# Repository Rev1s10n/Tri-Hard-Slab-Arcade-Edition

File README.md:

# Tri-Hard Slab: Arcade Edition
## **English | [繁體中文](README_zh-TW.md)**
A follow up from my previous [build](https://github.com/Rev1s10n/Tri-Hard-slab-v2), powered by [GP2040-CE](https://gp2040-ce.info/) firmware (v.0.7.10) with custom 16 buttons layout.<br>
This time it's made with Cherry MX switches instead of Kailh Choc switches, and CNC aluminum case with acrylic top layer for art insert.

**I would suggest not build this yourself at this momemnt as there's some design flaws, which makes it really difficult to assemble**<br>
**A new case design might come in the future**

## Key features and specs
- Dimensions: 270x200x24.1mm (including custom laser cut foampad)
- Weights: 1.3 kg
- Single CNC alumium case with laser cut acrylic sheet top panel and CNC polycarbonate mounting plate.
- Main key switches: any Cherry MX style switches, with hot swap sockets and Punk Workshop's key caps (25.5mm)
- Double RGB LED per key, and 4 RGB LEDs for player number indication.
- 2 USB Type-A connectors for passthrough devices, with slide switches to choose which one to activate.
- 1.3 inches OLED display.
- 3 slide switches on the top side for focus, SOCD and DP / LS / RS switch.
- Additional up button for general gaming purpose, and function key for quick profile swap.

Close up photos and feature explain:

_Fully redesigned circuit board with custom layout for my own comfort, passthrough device is now within the enclosure_

_1 additional tactile switch for function key, and custom display layout_

_Passthrough device can be selected with this slide switch_

_This time these switches is on the top side_

## Production files
Simply download all production files via Hardware files folder, and utilize services like JLCPCB (which is what I did in this case) to order the board.<br>
The board need standard PCBA for certain components. JLCPCB might told you there's some error (2 pins on 1 pad) but it's intended, and they'll make the board nevertheless.<br>
As for the case and acrylics / PC sheet, there's a step file for CNC aluminum case, 2 dxf files for laser cut acrylic, 1 dxf for CNC PC mounting plate.

## Source files
The Tri-Hard Slab AE is made with Autodesk Fusion 360 and KiCad 7.0.<br>
Everything is under Source files, include a rough Fusion 360 sketch which is the base of all laser-cut dxf files, step file and for KiCad to align things up.

## Assemble and settings
This is a bit tricky compare to original build.<br>
Here's some additional things you need to complete this build:
- Cherry MX switches, or any MX compatible switches, I use Cherry MX Black in this case.
- 16 Kailh MX hot swap socket (PG1511).
- 1.3 inches OLED display, make sure the pin order and set the slide switch accordingly.
- 9 M6 sex bolt / Chicago screws, with additional sink head screws
- Tons of hard and soft PVC washer (M6 sizes, 1mm thick) and NBR o-ring (6*2mm) for spacing.
- Custom laser cut EVA foams

There's a custom firmware with custom button layout for OLED display, and here's the GPIO pin mapping for reference:
|Keys|GPIO|
|-|-|
|Up|11|
|Down|9|
|Left|8|
|Right|10|
|B1/1K/A/Circle|13|
|B2/2K/B/Cross|15|
|B3/1P/X/Square|14|
|B4/2P/Y/Triangle|20|
|L1/4P/LB|18|
|R1/3P/RB|19|
|L2/4K/LT|17|
|R2/3K/RT|16|
|S1/Select/Back|1|
|S2/Start|3|
|L3/LS|21|
|R3/RS|22|
|A1/Home/Guide|2|
|A2/Touch|12|
|Function|0|
|Dual Direction Up|7|

Additional GPIO pin mapping and LED index for other features:
|Features|GPIO and index|
|-|-|
|RGB LED Data Pin|6|
|Player LEDs|starting from 32 to 35|
|Display SDA|4|
|Display SCL|5|
|Joystick Selection Slider Pin 1|26|
|Joystick Selection Slider Pin 2|25|
|SOCD Cleaning Mode Selection Slider Pin 1|28|
|SOCD Cleaning Mode Selection Slider Pin 2|27|
|PS Passthrough D+|23|
|PS Passthrough D-|24|
|Focus Mode Pin|29|

After load the setting file, there's 4 different profiles and there's shortcut combination to switch to any profile:
|Profile|Key combination|
|-|-|
|Profile 1 (Default pin mapping)|FN + S1 + S2 + 1P|
|Profile 2 (Unbind DDI Up)|FN + S1 + S2 + 2P|
|Profile 3 (Bind A2 as S1 for PC/Xbox)|FN + S1 + S2 + 3P|
|Profile 4 (Profile 3 + Unbind DDI Up)|FN + S1 + S2 + 4P|

## Custom artwork

You can download the PSD file and dxf drawing reference in Custom artwork template folder for top panel.<br>
Print it out and insert the artwork between 02 and 03 acrylic layers.

## Attribution
You're free to use this design as long as you credit to this page.<br>
[Licensed under CC BY 4.0](https://creativecommons.org/licenses/by/4.0/)

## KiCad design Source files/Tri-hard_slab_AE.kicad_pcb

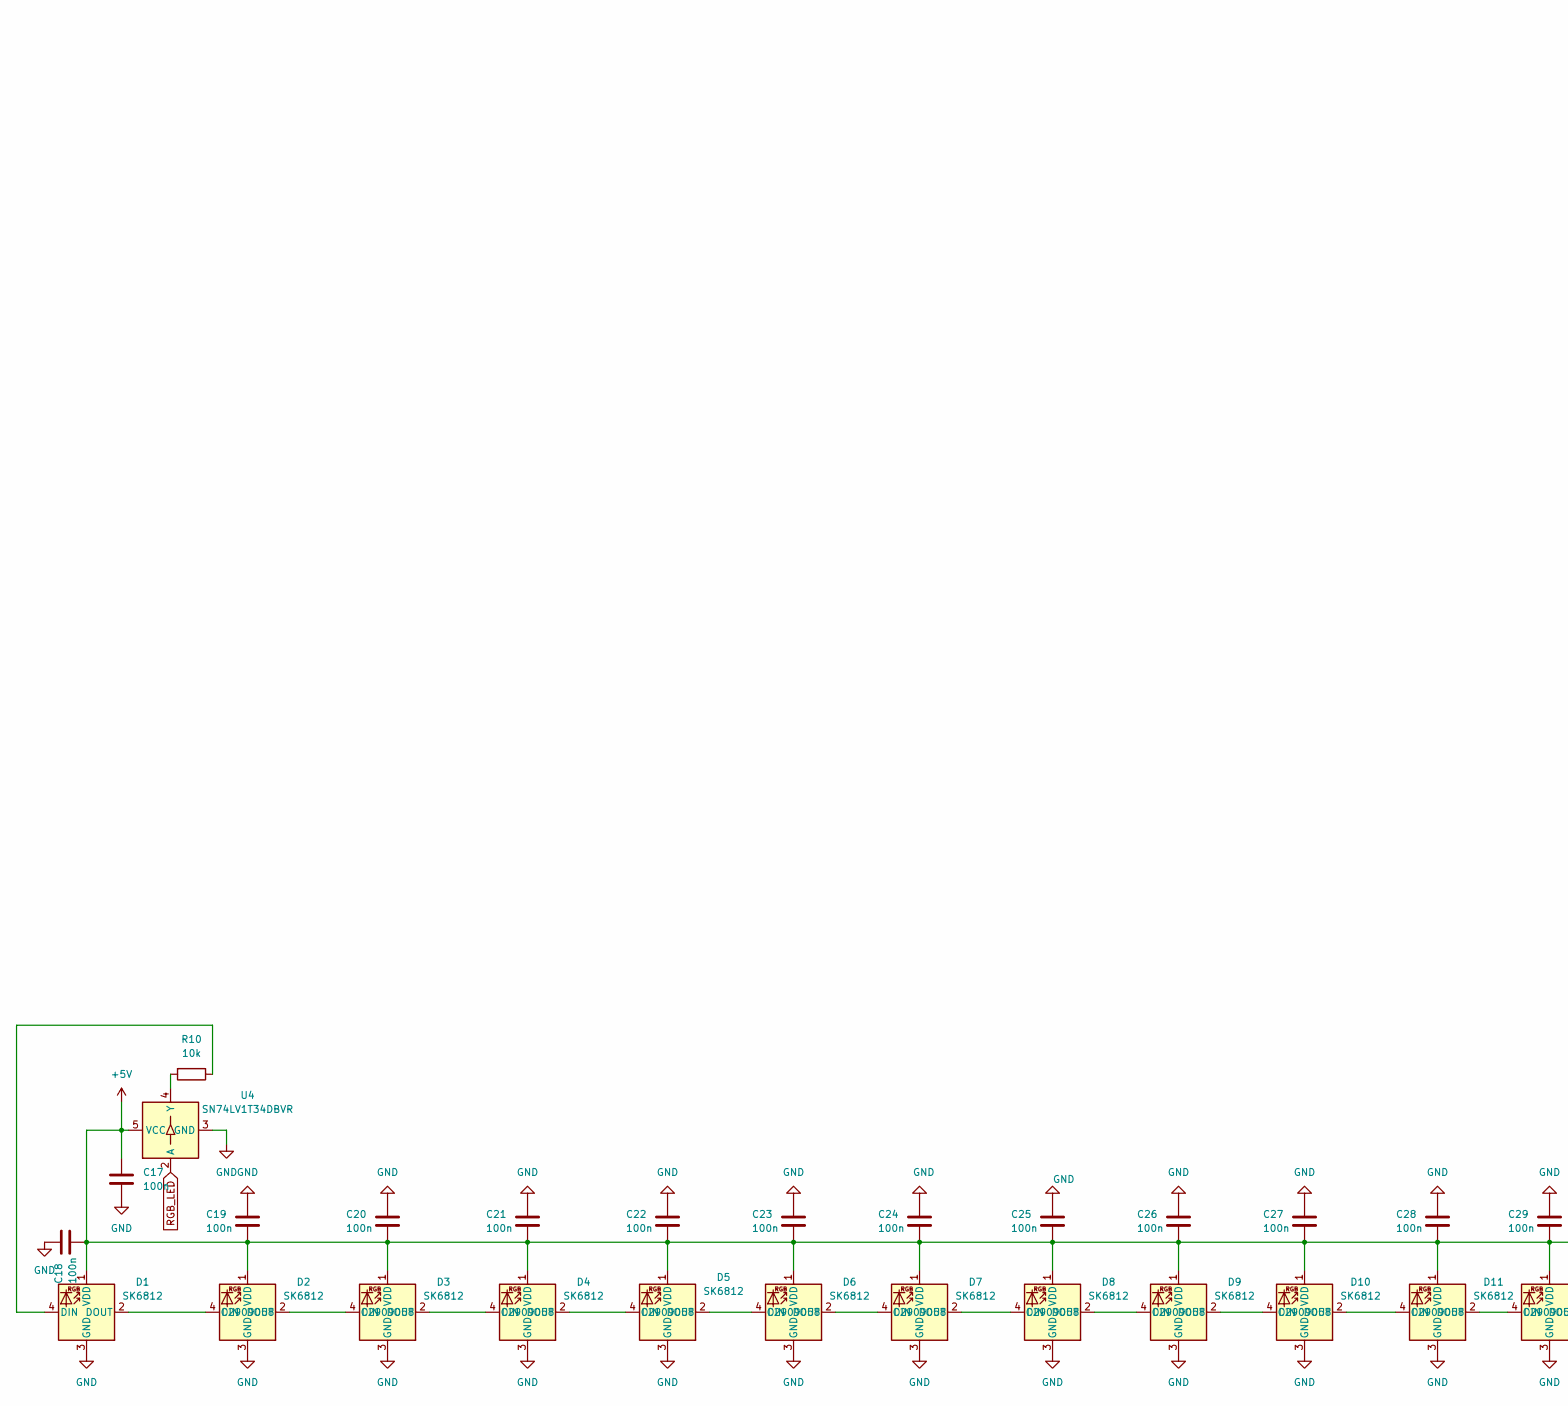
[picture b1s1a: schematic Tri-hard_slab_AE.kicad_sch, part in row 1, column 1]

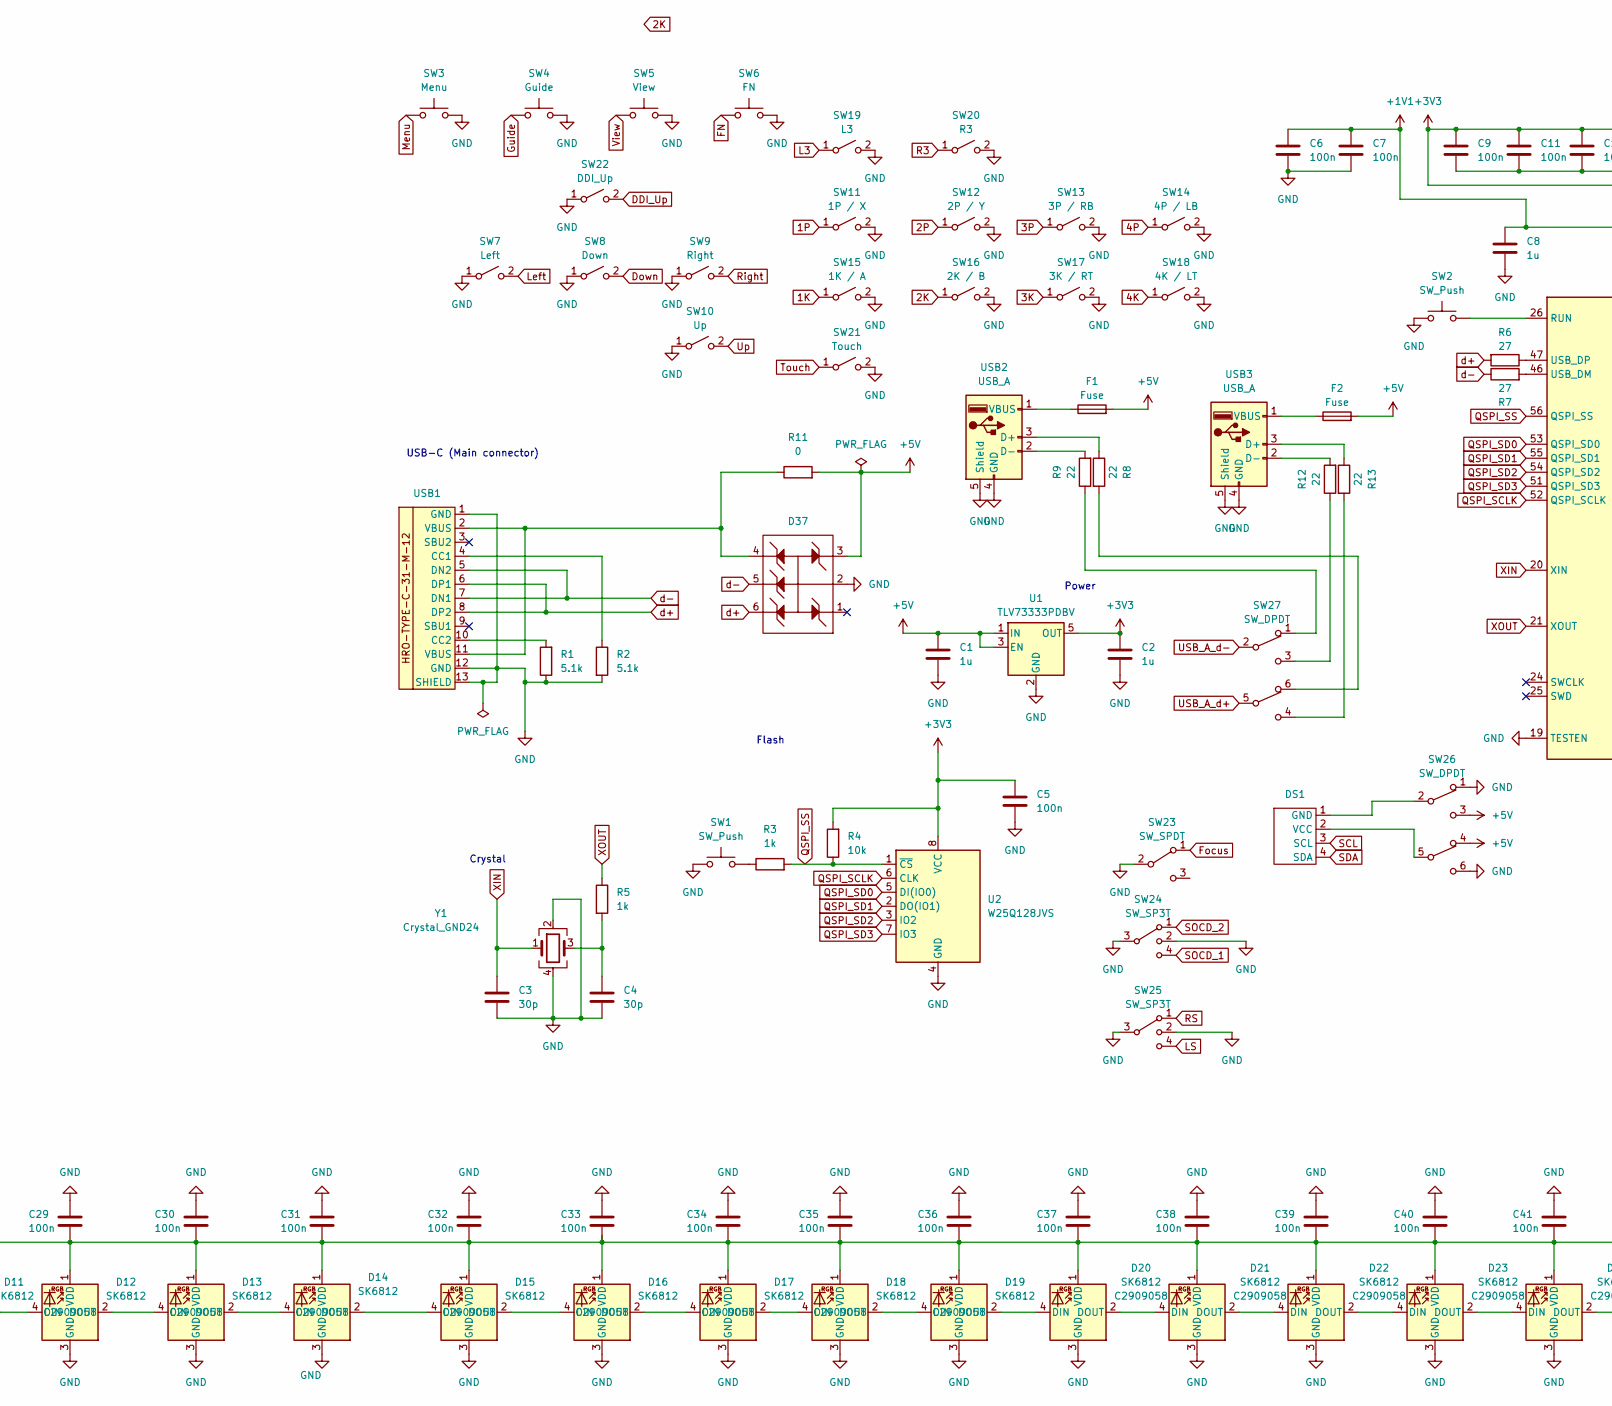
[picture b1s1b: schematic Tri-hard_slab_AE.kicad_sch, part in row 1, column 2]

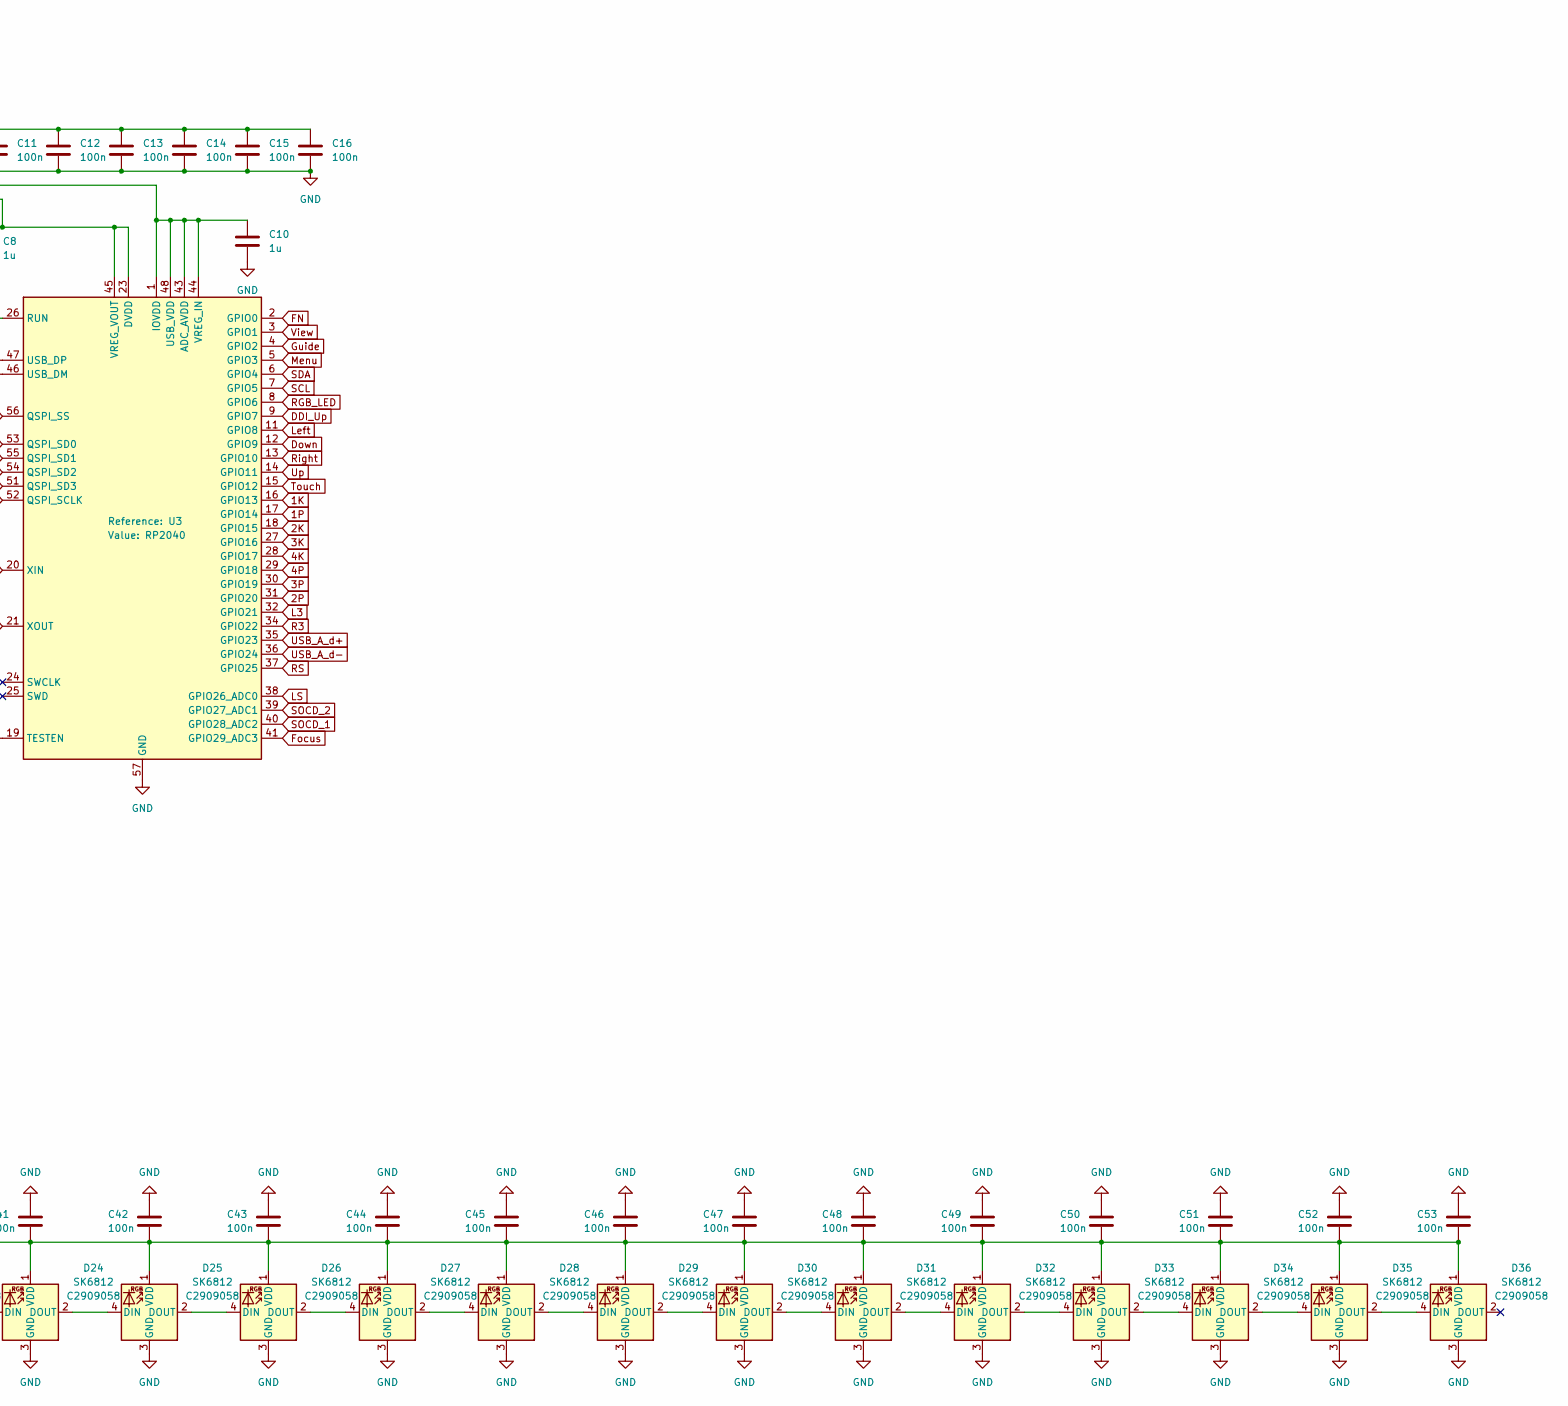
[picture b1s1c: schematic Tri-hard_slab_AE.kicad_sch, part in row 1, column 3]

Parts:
C1, C2, C8, C10: 1u; C_0402_1005Metric; LCSC C52923
C3, C4: 30p; C_0402_1005Metric; LCSC C161152
C5, C6, C7, C9, C11, C12, C13, C14, C15, C16, C17, C18, C19, C20, C21, C22, C23, C24, C25, C26, C27, C28, C29, C30, C31, C32, C33, C34, C35, C36, C37, C38, C39, C40, C41, C42, C43, C44, C45, C46, C47, C48, C49, C50, C51, C52, C53: 100n; C_0402_1005Metric; LCSC C1525
D1, D2, D3, D4, D5, D6, D7, D8, D9, D10, D11, D12, D13, D14, D15, D16, D17, D18, D19, D20, D21, D22, D23, D24, D25, D26, D27, D28, D29, D30, D31, D32, D33, D34, D35, D36: SK6812; SK6812-EC20; LCSC C2909058
D37: SOT-363_SC-70-6; LCSC C15879
DS1: 368030501246
F1, F2: Fuse; Fuse_0805_2012Metric; LCSC C116170
R1, R2: 5.1k; R_0402_1005Metric; LCSC C25905
R3, R5: 1k; R_0402_1005Metric; LCSC C11702
R4, R10: 10k; R_0402_1005Metric; LCSC C25744
R6, R7: 27; R_0402_1005Metric; LCSC C138021
R8, R9, R12, R13: 22; R_0603_1608Metric; LCSC C23345
R11: 0; R_0402_1005Metric; LCSC C17168
SW1, SW2: SW_Push; SKRAAKE010; LCSC C115354
SW3: Menu; TSF001A16026A; LCSC C2888706
SW4: Guide; TSF001A16026A; LCSC C2888706
SW5: View; TSF001A16026A; LCSC C2888706
SW6: FN; TSF001A16026A; LCSC C2888706
SW7: Left; SW_Hotswap_Kailh_MX_Plated
SW8: Down; SW_Hotswap_Kailh_MX_Plated
SW9: Right; SW_Hotswap_Kailh_MX_Plated
SW10: Up; SW_Hotswap_Kailh_MX_Plated
SW11: 1P / X; SW_Hotswap_Kailh_MX_Plated
SW12: 2P / Y; SW_Hotswap_Kailh_MX_Plated
SW13: 3P / RB; SW_Hotswap_Kailh_MX_Plated
SW14: 4P / LB; SW_Hotswap_Kailh_MX_Plated
SW15: 1K / A; SW_Hotswap_Kailh_MX_Plated
SW16: 2K / B; SW_Hotswap_Kailh_MX_Plated
SW17: 3K / RT; SW_Hotswap_Kailh_MX_Plated
SW18: 4K / LT; SW_Hotswap_Kailh_MX_Plated
SW19: L3; SW_Hotswap_Kailh_MX_Plated
SW20: R3; SW_Hotswap_Kailh_MX_Plated
SW21: Touch; SW_Hotswap_Kailh_MX_Plated
SW22: DDI_Up; SW_Hotswap_Kailh_MX_Plated
SW23: SW_SPDT; SHOU HAN SK12D07VG3; LCSC C431547
SW24, SW25: SW_SP3T; SHOU HAN SK13D07VG3; LCSC C2681580
SW26: SW_DPDT; MS-22C01-G010; LCSC C2837066
SW27: SW_DPDT; SS-22G88-G090; LCSC C2848925
U1: TLV73333PDBV; SOT-23-5; LCSC C134139
U2: W25Q128JVS; SOIC-8_5.23x5.23mm_P1.27mm
U3: RP2040; RP2040-QFN-56; LCSC C2040
U4: SN74LV1T34DBVR; SOT-23-5; LCSC C100024
USB1: HRO TYPE-C-31-M-08A; LCSC C2848616
USB2, USB3: USB_A; U-A-24DD-W-16; LCSC C2689981
Y1: Crystal_GND24; Crystal_SMD_3225-4Pin_3.2x2.5mm; LCSC C9002

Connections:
1K: SW15.1 (A), U3.16 (GPIO13)
1P: SW11.1 (A), U3.17 (GPIO14)
2K: SW16.1 (A), U3.18 (GPIO15)
2P: SW12.1 (A), U3.31 (GPIO20)
3K: SW17.1 (A), U3.27 (GPIO16)
3P: SW13.1 (A), U3.30 (GPIO19)
4K: SW18.1 (A), U3.28 (GPIO17)
4P: SW14.1 (A), U3.29 (GPIO18)
+1V1: C6.1, C7.1, C8.1, U3.23 (DVDD), U3.45 (VREG_VOUT), U3.50 (DVDD)
+3V3: C2.1, C5.1, C9.1, C10.1, C11.1, C12.1, C13.1, C14.1, C15.1, C16.1, R4.2, U1.5 (OUT), U2.8 (VCC), U3.1 (IOVDD), U3.10 (IOVDD), U3.22 (IOVDD), U3.33 (IOVDD), U3.42 (IOVDD), U3.43 (ADC_AVDD), U3.44 (VREG_IN), U3.48 (USB_VDD), U3.49 (IOVDD)
+5V: C1.1, C17.1, C18.1, C19.1, C20.1, C21.1, C22.1, C23.1, C24.1, C25.1, C26.1, C27.1, C28.1, C29.1, C30.1, C31.1, C32.1, C33.1, C34.1, C35.1, C36.1, C37.1, C38.1, C39.1, C40.1, C41.1, C42.1, C43.1, C44.1, C45.1, C46.1, C47.1, C48.1, C49.1, C50.1, C51.1, C52.1, C53.1, D1.1 (VDD), D2.1 (VDD), D3.1 (VDD), D4.1 (VDD), D5.1 (VDD), D6.1 (VDD), D7.1 (VDD), D8.1 (VDD), D9.1 (VDD), D10.1 (VDD), D11.1 (VDD), D12.1 (VDD), D13.1 (VDD), D14.1 (VDD), D15.1 (VDD), D16.1 (VDD), D17.1 (VDD), D18.1 (VDD), D19.1 (VDD), D20.1 (VDD), D21.1 (VDD), D22.1 (VDD), D23.1 (VDD), D24.1 (VDD), D25.1 (VDD), D26.1 (VDD), D27.1 (VDD), D28.1 (VDD), D29.1 (VDD), D30.1 (VDD), D31.1 (VDD), D32.1 (VDD), D33.1 (VDD), D34.1 (VDD), D35.1 (VDD), D36.1 (VDD), D37.3, F1.2, F2.2, R11.2, SW26.3 (C), SW26.4 (A), U1.1 (IN), U1.3 (EN), U4.5 (VCC)
DDI_Up: SW22.2 (B), U3.9 (GPIO7)
Down: SW8.2 (B), U3.12 (GPIO9)
FN: SW6.1, U3.2 (GPIO0)
Focus: SW23.1 (A), U3.41 (GPIO29_ADC3)
GND: C1.2, C2.2, C3.2, C4.2, C5.2, C6.2, C7.2, C8.2, C9.2, C10.2, C11.2, C12.2, C13.2, C14.2, C15.2, C16.2, C17.2, C18.2, C19.2, C20.2, C21.2, C22.2, C23.2, C24.2, C25.2, C26.2, C27.2, C28.2, C29.2, C30.2, C31.2, C32.2, C33.2, C34.2, C35.2, C36.2, C37.2, C38.2, C39.2, C40.2, C41.2, C42.2, C43.2, C44.2, C45.2, C46.2, C47.2, C48.2, C49.2, C50.2, C51.2, C52.2, C53.2, D1.3 (GND), D2.3 (GND), D3.3 (GND), D4.3 (GND), D5.3 (GND), D6.3 (GND), D7.3 (GND), D8.3 (GND), D9.3 (GND), D10.3 (GND), D11.3 (GND), D12.3 (GND), D13.3 (GND), D14.3 (GND), D15.3 (GND), D16.3 (GND), D17.3 (GND), D18.3 (GND), D19.3 (GND), D20.3 (GND), D21.3 (GND), D22.3 (GND), D23.3 (GND), D24.3 (GND), D25.3 (GND), D26.3 (GND), D27.3 (GND), D28.3 (GND), D29.3 (GND), D30.3 (GND), D31.3 (GND), D32.3 (GND), D33.3 (GND), D34.3 (GND), D35.3 (GND), D36.3 (GND), D37.2, R1.1, R2.2, SW1.1, SW2.1, SW3.2, SW4.2, SW5.2, SW6.2, SW7.1 (A), SW8.1 (A), SW9.1 (A), SW10.1 (A), SW11.2 (B), SW12.2 (B), SW13.2 (B), SW14.2 (B), SW15.2 (B), SW16.2 (B), SW17.2 (B), SW18.2 (B), SW19.2 (B), SW20.2 (B), SW21.2 (B), SW22.1 (A), SW23.2 (B), SW23.GND, SW24.2, SW24.3, SW24.GND, SW25.2, SW25.3, SW25.GND, SW26.1 (A), SW26.6 (C), U1.2 (GND), U2.4 (GND), U3.19 (TESTEN), U3.57 (GND), U4.3 (GND), USB1.1 (GND), USB1.12 (GND), USB1.13 (SHIELD), USB2.4 (GND), USB2.5 (Shield), USB3.4 (GND), USB3.5 (Shield), Y1.2, Y1.4
Guide: SW4.1, U3.4 (GPIO2)
L3: SW19.1 (A), U3.32 (GPIO21)
LS: SW25.4, U3.38 (GPIO26_ADC0)
Left: SW7.2 (B), U3.11 (GPIO8)
Menu: SW3.1, U3.5 (GPIO3)
unnamed: C4.1, R5.2, Y1.3
unnamed: D1.4 (DIN), R10.1
unnamed: D1.2 (DOUT), D2.4 (DIN)
unnamed: D2.2 (DOUT), D3.4 (DIN)
unnamed: D3.2 (DOUT), D4.4 (DIN)
unnamed: D4.2 (DOUT), D5.4 (DIN)
unnamed: D5.2 (DOUT), D6.4 (DIN)
unnamed: D6.2 (DOUT), D7.4 (DIN)
unnamed: D7.2 (DOUT), D8.4 (DIN)
unnamed: D8.2 (DOUT), D9.4 (DIN)
unnamed: D9.2 (DOUT), D10.4 (DIN)
unnamed: D10.2 (DOUT), D11.4 (DIN)
unnamed: D11.2 (DOUT), D12.4 (DIN)
unnamed: D12.2 (DOUT), D13.4 (DIN)
unnamed: D13.2 (DOUT), D14.4 (DIN)
unnamed: D14.2 (DOUT), D15.4 (DIN)
unnamed: D15.2 (DOUT), D16.4 (DIN)
unnamed: D16.2 (DOUT), D17.4 (DIN)
unnamed: D17.2 (DOUT), D18.4 (DIN)
unnamed: D18.2 (DOUT), D19.4 (DIN)
unnamed: D19.2 (DOUT), D20.4 (DIN)
unnamed: D20.2 (DOUT), D21.4 (DIN)
unnamed: D21.2 (DOUT), D22.4 (DIN)
unnamed: D22.2 (DOUT), D23.4 (DIN)
unnamed: D23.2 (DOUT), D24.4 (DIN)
unnamed: D24.2 (DOUT), D25.4 (DIN)
unnamed: D25.2 (DOUT), D26.4 (DIN)
unnamed: D26.2 (DOUT), D27.4 (DIN)
unnamed: D27.2 (DOUT), D28.4 (DIN)
unnamed: D28.2 (DOUT), D29.4 (DIN)
unnamed: D29.2 (DOUT), D30.4 (DIN)
unnamed: D30.2 (DOUT), D31.4 (DIN)
unnamed: D31.2 (DOUT), D32.4 (DIN)
unnamed: D32.2 (DOUT), D33.4 (DIN)
unnamed: D33.2 (DOUT), D34.4 (DIN)
unnamed: D34.2 (DOUT), D35.4 (DIN)
unnamed: D35.2 (DOUT), D36.4 (DIN)
unnamed: D37.4, R11.1, USB1.2 (VBUS), USB1.11 (VBUS)
unnamed: DS1.1 (GND), SW26.2 (B)
unnamed: DS1.2 (VCC), SW26.5 (B)
unnamed: R3.1, SW1.2
unnamed: R8.2, SW27.6 (A)
unnamed: R9.1, SW27.1 (A)
unnamed: R12.1, SW27.3 (C)
unnamed: R13.2, SW27.4 (C)
unnamed: SW2.2, U3.26 (RUN)
unnamed: R7.2, U3.46 (USB_DM)
unnamed: R6.1, U3.47 (USB_DP)
unnamed: R10.2, U4.4 (Y)
unnamed: R2.1, USB1.4 (CC1)
unnamed: R1.2, USB1.10 (CC2)
unnamed: R8.1, USB2.3 (D+)
unnamed: R9.2, USB2.2 (D-)
unnamed: F1.1, USB2.1 (VBUS)
unnamed: R13.1, USB3.3 (D+)
unnamed: R12.2, USB3.2 (D-)
unnamed: F2.1, USB3.1 (VBUS)
QSPI_SCLK: U2.6 (CLK), U3.52 (QSPI_SCLK)
QSPI_SD0: U2.5 (DI(IO0)), U3.53 (QSPI_SD0)
QSPI_SD1: U2.2 (DO(IO1)), U3.55 (QSPI_SD1)
QSPI_SD2: U2.3 (IO2), U3.54 (QSPI_SD2)
QSPI_SD3: U2.7 (IO3), U3.51 (QSPI_SD3)
QSPI_SS: R3.2, R4.1, U2.1 (~CS), U3.56 (QSPI_SS)
R3: SW20.1 (A), U3.34 (GPIO22)
RGB_LED: U3.8 (GPIO6), U4.2 (A)
RS: SW25.1, U3.37 (GPIO25)
Right: SW9.2 (B), U3.13 (GPIO10)
SCL: DS1.3 (SCL), U3.7 (GPIO5)
SDA: DS1.4 (SDA), U3.6 (GPIO4)
SOCD_1: SW24.4, U3.40 (GPIO28_ADC2)
SOCD_2: SW24.1, U3.39 (GPIO27_ADC1)
Touch: SW21.1 (A), U3.15 (GPIO12)
USB_A_d+: SW27.5 (B), U3.35 (GPIO23)
USB_A_d-: SW27.2 (B), U3.36 (GPIO24)
Up: SW10.2 (B), U3.14 (GPIO11)
View: SW5.1, U3.3 (GPIO1)
XIN: C3.1, U3.20 (XIN), Y1.1
XOUT: R5.1, U3.21 (XOUT)
d+: D37.6, R6.2, USB1.6 (DP1), USB1.8 (DP2)
d-: D37.5, R7.1, USB1.5 (DN2), USB1.7 (DN1)

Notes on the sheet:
Crystal
USB-C (Main connector)
Flash
Power

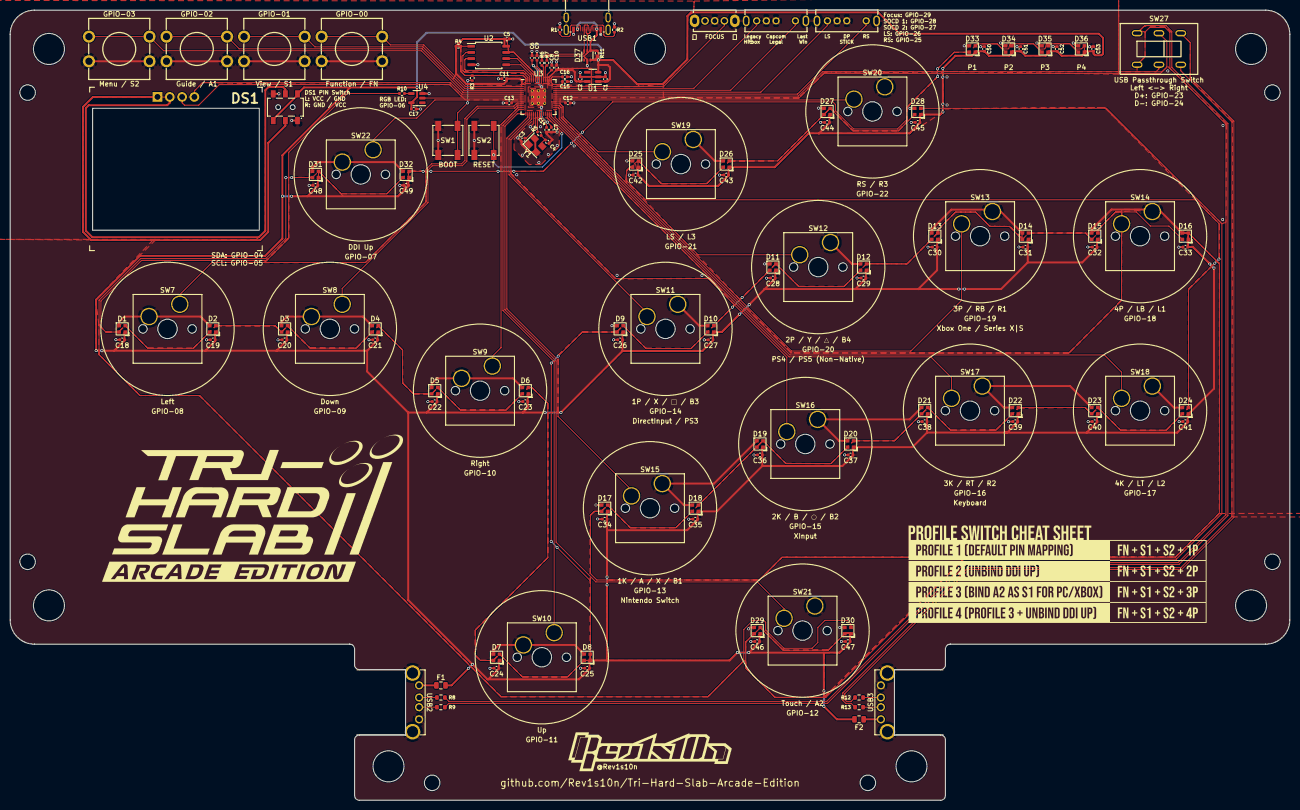
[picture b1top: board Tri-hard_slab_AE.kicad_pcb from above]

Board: 2 copper layers, 264.0 x 163.0 mm, 141 parts (0 on the bottom side), 101 nets.

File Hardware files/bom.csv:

Designator,Footprint,Quantity,Value,LCSC Part #
"C1, C10, C2, C8",0402,4,1u,C52923
"C11, C12, C13, C14, C15, C16, C17, C18, C19, C20, C21, C22, C23, C24, C25, C26, C27, C28, C29, C30, C31, C32, C33, C34, C35, C36, C37, C38, C39, C40, C41, C42, C43, C44, C45, C46, C47, C48, C49, C5, C50, C51, C52, C53, C6, C7, C9",0402,47,100n,C1525
"C3, C4",0402,2,30p,C161152
"D1, D10, D11, D12, D13, D14, D15, D16, D17, D18, D19, D2, D20, D21, D22, D23, D24, D25, D26, D27, D28, D29, D3, D30, D31, D32, D33, D34, D35, D36, D4, D5, D6, D7, D8, D9",SK6812-EC20,36,SK6812,C2909058
D37,SOT-363_SC-70-6,1,~,C15879
DS1,368030501246,1,~,
"F1, F2",0805,2,Fuse,C116170
"R1, R2",0402,2,5.1k,C25905
"R10, R4",0402,2,10k,C25744
R11,0402,1,0,C17168
"R12, R13, R8, R9",0603,4,22,C23345
"R3, R5",0402,2,1k,C11702
"R6, R7",0402,2,27,C138021
"SW1, SW2",SKRAAKE010,2,SW_Push,C115354
SW10,SW_Hotswap_Kailh_MX_Plated,1,Up,
SW11,SW_Hotswap_Kailh_MX_Plated,1,1P / X,
SW12,SW_Hotswap_Kailh_MX_Plated,1,2P / Y,
SW13,SW_Hotswap_Kailh_MX_Plated,1,3P / RB,
SW14,SW_Hotswap_Kailh_MX_Plated,1,4P / LB,
SW15,SW_Hotswap_Kailh_MX_Plated,1,1K / A,
SW16,SW_Hotswap_Kailh_MX_Plated,1,2K / B,
SW17,SW_Hotswap_Kailh_MX_Plated,1,3K / RT,
SW18,SW_Hotswap_Kailh_MX_Plated,1,4K / LT,
SW19,SW_Hotswap_Kailh_MX_Plated,1,L3,
SW20,SW_Hotswap_Kailh_MX_Plated,1,R3,
SW21,SW_Hotswap_Kailh_MX_Plated,1,Touch,
SW22,SW_Hotswap_Kailh_MX_Plated,1,DDI_Up,
SW23,SHOU HAN SK12D07VG3,1,SW_SPDT,C431547
"SW24, SW25",SHOU HAN SK13D07VG3,2,SW_SP3T,C2681580
SW26,MS-22C01-G010,1,SW_DPDT,C2837066
SW27,SS-22G88-G090,1,SW_DPDT,C2848925
SW3,TSF001A16026A,1,Menu,C2888706
SW4,TSF001A16026A,1,Guide,C2888706
SW5,TSF001A16026A,1,View,C2888706
SW6,TSF001A16026A,1,FN,C2888706
SW7,SW_Hotswap_Kailh_MX_Plated,1,Left,
SW8,SW_Hotswap_Kailh_MX_Plated,1,Down,
SW9,SW_Hotswap_Kailh_MX_Plated,1,Right,
U1,SOT-23-5,1,TLV73333PDBV,C134139
U2,SOIC-8_5.23x5.23mm_P1.27mm,1,W25Q128JVS,
U3,RP2040-QFN-56,1,RP2040,C2040
U4,SOT-23-5,1,SN74LV1T34DBVR,C100024
USB1,HRO TYPE-C-31-M-08A,1,~,C2848616
"USB2, USB3",U-A-24DD-W-16,2,USB_A,C2689981
Y1,Crystal_SMD_3225-4Pin_3.2x2.5mm,1,Crystal_GND24,C9002

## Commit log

2024-03-24 Create temp
2024-11-26 Fixed mislabeled L3/R3 GPIO pins.
2024-11-26 Update firmware version with latest GP2040-CE release
2024-11-26 Update README.md as I'm using 0.7.10 now
2024-11-26 Update README_zh-TW.md as I'm using 0.7.10 now
2025-04-18 Rename Firmware and setting files/GP2040-CE_0.7.10_Tri-HardSlabAE.uf2 to Firmware and setting files/old version/0.7.10/GP2040-CE_0.7.10_Tri-HardSlabAE.uf2
    move to old version for archive
2025-04-18 Rename Firmware and setting files/gp2040ce_backup_20241126144613754.gp2040 to Firmware and setting files/old version/0.7.10/gp2040ce_backup_20241126144613754.gp2040
    move to old version for archive
2025-04-18 Rename Firmware and setting files/old version/GP2040-CE_0.7.7_Tri-HardSlabAE.uf2 to Firmware and setting files/old version/0.7.7/GP2040-CE_0.7.7_Tri-HardSlabAE.uf2
    move to old version for archive
2025-04-18 Rename Firmware and setting files/old version/gp2040ce_backup_20240324161520429.gp2040 to Firmware and setting files/old version/0.7.7/gp2040ce_backup_20240324161520429.gp2040
    move to old version for archive
2025-04-18 Latest firmware based on GP2040-CE 0.7.11 release
2025-04-18 moving files
2025-07-14 Create BoardConfig.h
    BoardConfig for this board.
2025-07-14 Create Tri-Hard_Slab-AE.h
    Board setting files related to this board.
